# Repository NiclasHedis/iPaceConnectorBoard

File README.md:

# Jaguar-iPace-Inverter connector board

This PCB is used to replace the OEM board for the 28pin connector interfacing the vehicle harness when using the Openinverter iPace main board. (https://github.com/damienmaguire/Jaguar-iPace-Inverter)

## Instructions:
Original J1 (28pin TE connector mounted in the housing) is used, FPC-connector is the same so the original flex cable is reused, same with the water temp sensor.  
Just mount the board and solder the 28pin connector.

The OEM pcb is using a press fit connector, so use a flat screwdriver to remove it by bending from different directions.

### Components:
* R1, R2 - 0805 10kOhm.
* J1 - OEM in housing
* J2 - Hirose ZE05H-2P-2V - https://mou.sr/3UHuiN9
* J3 - Kyocera 046810650020846+T - https://mou.sr/4iiVvzu

### Logbook:
2026-09-10: First revision ordered by Damien from JLCPCB.

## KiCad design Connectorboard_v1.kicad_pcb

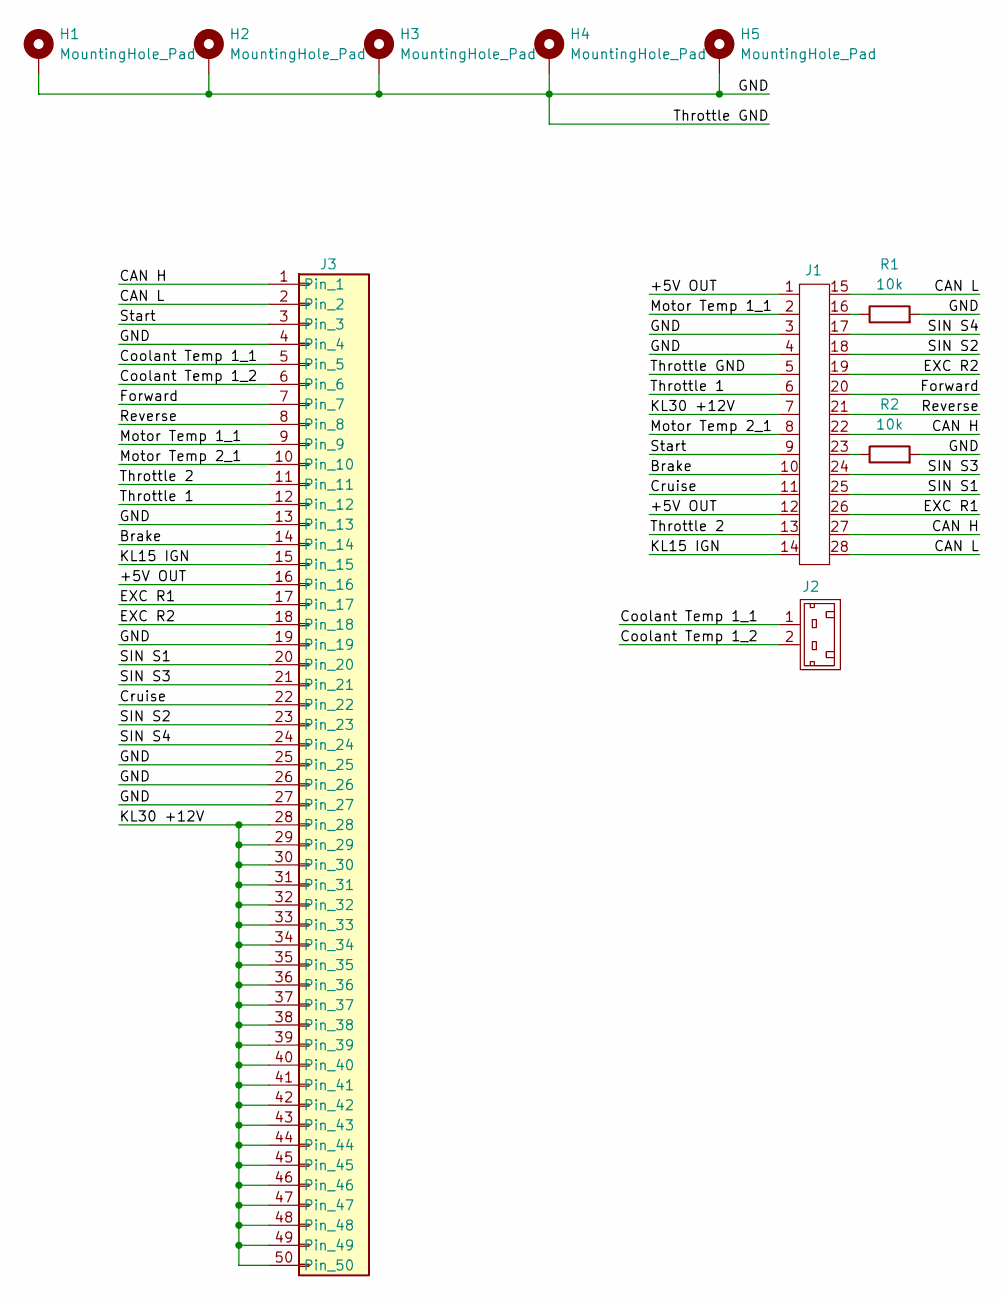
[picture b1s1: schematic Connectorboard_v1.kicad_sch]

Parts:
H1, H2, H3, H4, H5: MountingHole_Pad; MountingHole_4.5mm_Pad_Via
J1: 28-pos Male AMPSEAL 16
J2: ZE05H-2P-2V
J3: 046810650020846+T
R1, R2: 10k; R_0805_2012Metric_Pad1.20x1.40mm_HandSolder

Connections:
/+5V OUT: J1.1, J1.12, J3.16
/Brake: J1.10, J3.14
/CAN H: J1.22, J1.27, J3.1
/CAN L: J1.15, J1.28, J3.2
/Coolant Temp 1_1: J2.1, J3.5
/Coolant Temp 1_2: J2.2, J3.6
/Cruise: J1.11, J3.22
/EXC R1: J1.26, J3.17
/EXC R2: J1.19, J3.18
/Forward: J1.20, J3.7
/GND: H1.1, H2.1, H3.1, H4.1, H5.1, J1.3, J1.4, J1.5, J3.4, J3.13, J3.19, J3.25, J3.26, J3.27, J3.MP, R1.2, R2.2
/KL15 IGN: J1.14, J3.15
/KL30 +12V: J1.7, J3.28, J3.29, J3.30, J3.31, J3.32, J3.33, J3.34, J3.35, J3.36, J3.37, J3.38, J3.39, J3.40, J3.41, J3.42, J3.43, J3.44, J3.45, J3.46, J3.47, J3.48, J3.49, J3.50
/Motor Temp 1_1: J1.2, J3.9
/Motor Temp 2_1: J1.8, J3.10
/Reverse: J1.21, J3.8
/SIN S1: J1.25, J3.20
/SIN S2: J1.18, J3.23
/SIN S3: J1.24, J3.21
/SIN S4: J1.17, J3.24
/Start: J1.9, J3.3
/Throttle 1: J1.6, J3.12
/Throttle 2: J1.13, J3.11
unnamed: J1.16, R1.1
unnamed: J1.23, R2.1

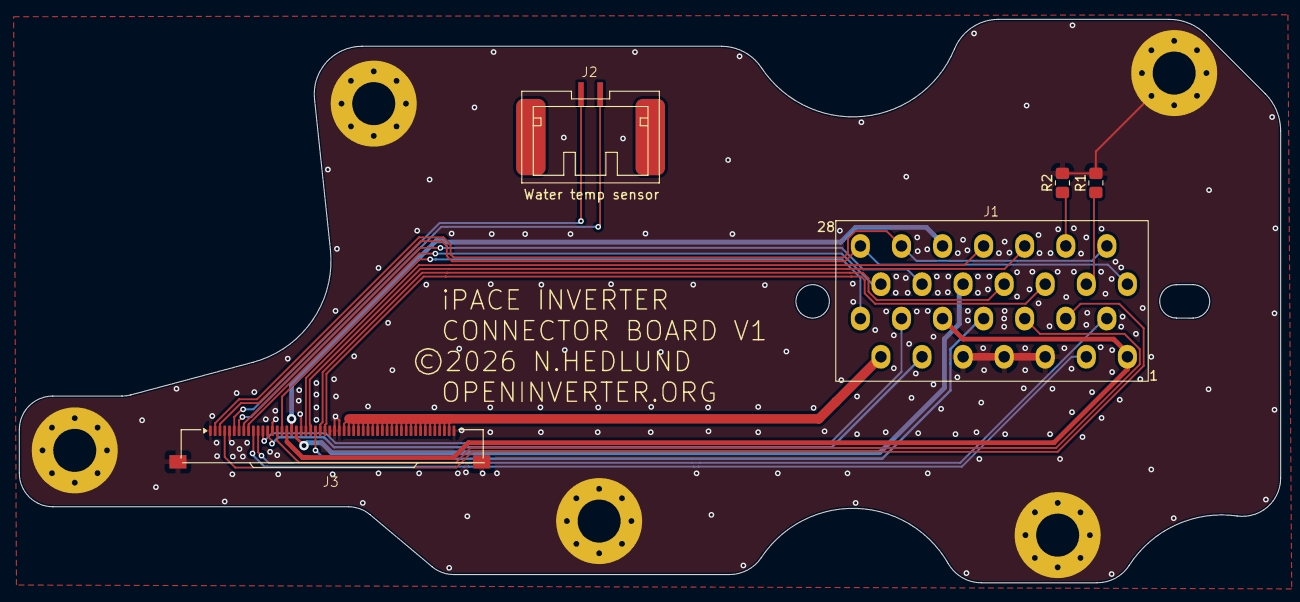
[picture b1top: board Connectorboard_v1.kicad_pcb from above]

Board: 2 copper layers, 132.0 x 59.0 mm, 10 parts (0 on the bottom side), 25 nets.

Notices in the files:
Connectorboard_v1.kicad_pcb:
©2026 N.HEDLUND
